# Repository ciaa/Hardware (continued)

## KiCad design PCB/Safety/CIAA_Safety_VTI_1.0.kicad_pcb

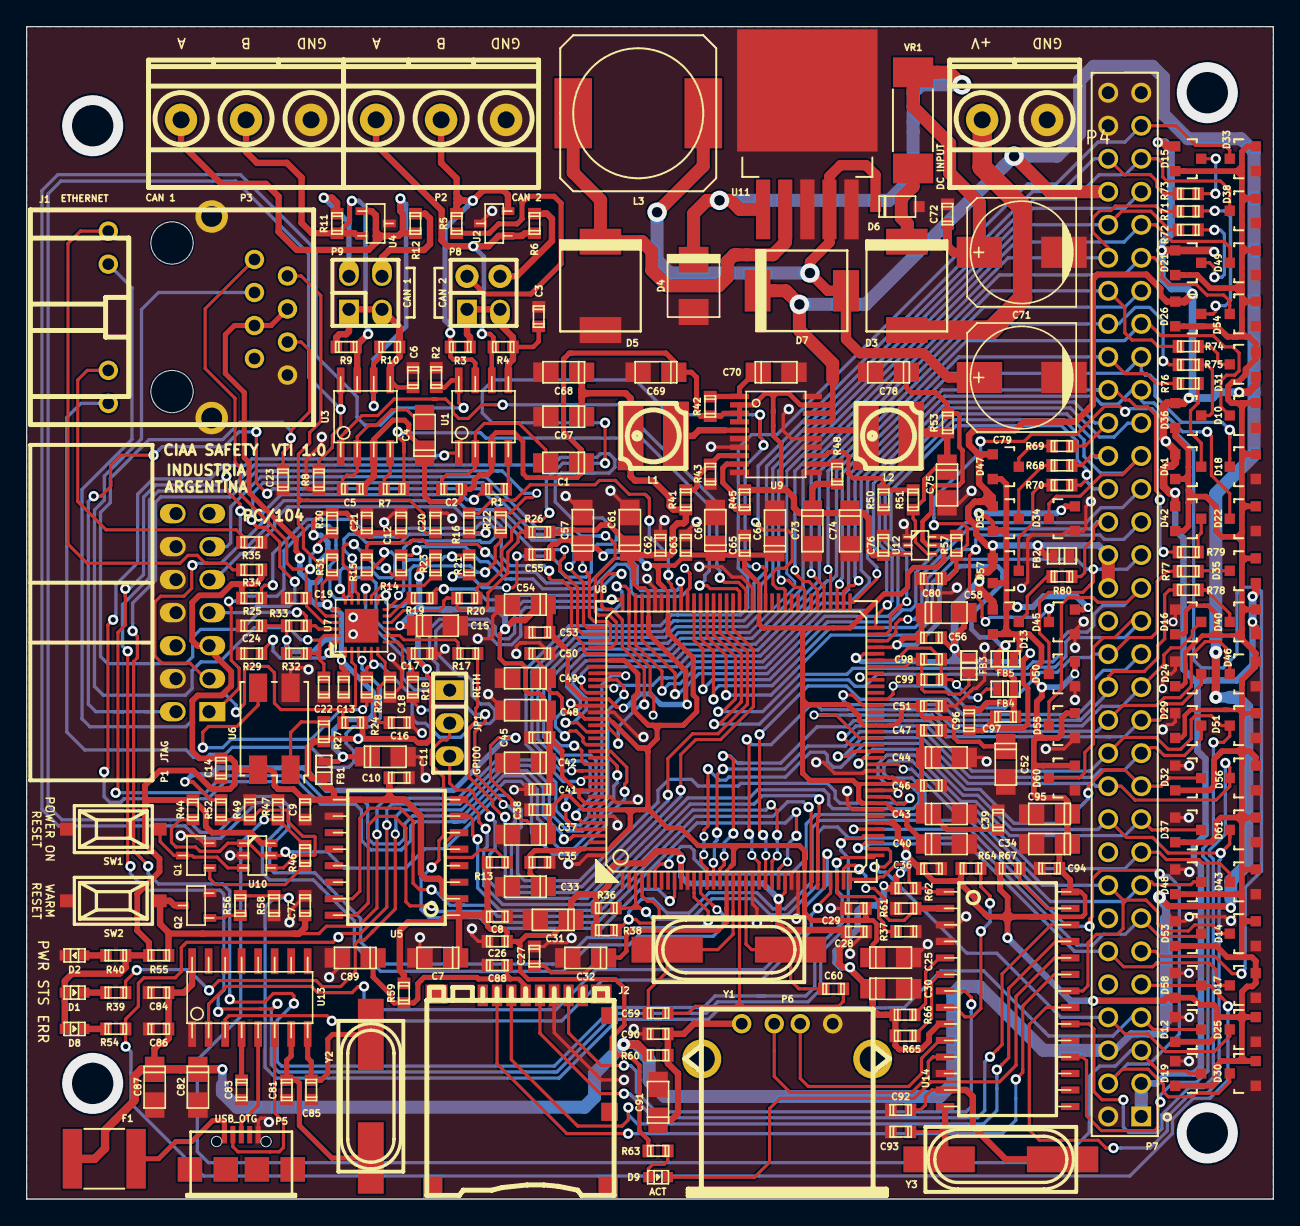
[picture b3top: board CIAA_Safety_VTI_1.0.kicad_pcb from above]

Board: 2 copper layers, 95.9 x 90.2 mm, 275 parts (0 on the bottom side), 191 nets.

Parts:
C1, C4, C7, C11, C15, C74, C82, C87, C89, C91, C95: 10uF-6.3V; c_tant_A
C2, C3, C5, C6, C8, C9, C10, C12, C13, C14, C17, C18, C21, C24, C26, C27, C28, C29, C35, C36, C38, C39, C41, C45, C46, C47, C50, C51, C53, C55, C56, C62, C63, C65, C72, C76, C83, C84, C86, C88, C90, C94, C98: 100nF; c_0603
C16: 470pF; c_0603
C19, C20, C22, C23: 18pF; c_0603
C25, C30, C31, C32, C33, C34, C37, C40, C42, C43, C44, C48, C49, C52, C54, C57, C58, C61, C64, C66: 10uF; c_tant_A
C59, C60: 33pF; c_0603
C67, C68, C69, C73, C75, C78: 22uF-6.3V; c_tant_A
C70: 1uF-6.3V; c_tant_A
C71: 470uF-50V; c_elec_8x10
C77: 1000pF; c_0603
C79: 330uF-16V; c_elec_8x10
C80: 4700pF; c_0603
C81, C85: 22pF; c_0603
C92, C93: 27pF; c_0603
C96, C97, C99: 10nF; c_0603
D1: STATUS; Led_0603
D2: PWR; Led_0603
D3, D7: MURS360; do214ab
D4: P6SMB33CA; do214aa
D5: MBRS540T3G; do214ab
D6: MMSZ5V6T1G; sod123
D8: ERR; Led_0603
D9: ACT; Led_0603
D10, D12, D13, D14, D15, D16, D17, D18, D19, D21, D22, D24, D25, D26, D29, D30, D31, D32, D33, D34, D35, D36, D37, D38, D40, D41, D42, D43, D45, D46, D47, D48, D49, D50, D51, D52, D53, D54, D55, D56, D57, D58, D60, D61: BAV199
F1: MF-SMDF050
FB1: BK1608HS220-T; inductor_smd_0603
FB2, FB5: MMZ1608B601C; inductor_smd_0603
FB3, FB4: ACML0603101; inductor_smd_0603
J1: HR911105A
J2: SD-CON; microsd_socket
JP1: JUMPER3; pin_strip_3
L1, L2: 1uH-3.1A; inductor_smd_4.8x2.8mm
L3: 47uH; SELF-WE-PD-XXL
P1: JTAG; vasch_strip_7x2_90
P2: CAN 2; mkds_1,5-3
P3: CAN 1; mkds_1,5-3
P4: DC INPUT; mkds_1,5-2
P5: USB_OTG; conn_usb_B_micro_smd-2
P6: USB_A; conn_usb_A
P7: CONN_02X32; bus_ISA_8bits
P8: CAN2; pin_socket_2x2
P9: CAN1; pin_socket_2x2
Q1, Q2: NDS7002A; sot23
R1, R7, R34, R35: 270; r_0603
R2, R8: 4K7; r_0603
R3, R4, R9, R10: 1.5K; r_0603
R5, R6, R11, R12: 60; r_0603
R13, R23, R24, R26, R36, R38, R43, R46, R50, R56, R68, R69, R70, R71, R72, R73, R74, R75, R76, R77, R78, R79, R80: 10K; r_0603
R14, R15, R16, R21, R22: 0; r_0603
R17, R18, R19, R20: 22; r_0603
R25: 1K5; r_0603
R27: 100K; r_0603
R28: 24.9; r_0603
R29: 12.1K; r_0603
R30, R31, R32, R33: 49,9; r_0603
R37, R39, R40, R44, R49, R52, R54, R55, R63: 2.2K; r_0603
R41, R57: 31.6K; r_0603
R42: 4.99; r_0603
R45, R48: 49.9K; r_0603
R47, R58: 330K; r_0603
R51: 5.76K; r_0603
R53: 0.010; r_0603
R59, R61, R62, R64, R65, R66, R67: 1K; r_0603
R60: 100; r_0603
SW1: POWER ON RESET; smd_push
SW2: WARM RESET; smd_push
U1, U3: SN65HVD1040; so-8
U2, U4: PESD1CAN; sot23
U5: S70FL01GS; soic-16
U6: Si502; Crystal_SMD_7050_4Pads
U7: LAN8720A-CP; qfn-24
U8: TMS570LS1227; TQFP-144
U9: LM26420; tssop-20
U10: TPS3106K33_DBV_6; sot23-6
U11: LM2596S-5.0; TO-263-5Lead
U12: INA210_DCK_6; sc70-6
U13: CH340G; so-16
U14: CH376S; soic-28
VR1: MF-SM300
Y1: 16MHz; hc-49_smd
Y2, Y3: 12MHz; hc-49_smd

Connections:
+1V2: C25.1, C27.1, C29.1, C32.1, C33.1, C35.2, C37.1, C38.2, C39.1, C40.1, C43.1, C44.1, C46.1, C47.1, C49.1, C50.2, C51.1, C52.1, C55.2, C57.1, C63.2, C64.1, C65.2, C66.1, C78.1, R52.1, R53.1, U8.17, U8.29, U8.45, U8.48, U8.49, U8.57, U8.87, U8.101, U8.114, U8.123, U8.137, U8.143, U12.5
+3.3VADC: C56.1, C58.1, C96.1, C97.1, FB4.1, FB5.2, U8.69
+3V3: C7.1, C8.1, C9.1, C10.1, C14.1, C15.1, C17.1, C26.1, C28.1, C30.1, C31.1, C34.1, C36.1, C41.2, C42.1, C45.2, C48.1, C53.2, C54.1, C61.1, C62.1, C67.1, C68.1, C94.1, C95.1, D1.2, D8.2, D10.1, D12.1, D13.1, D14.1, D15.1, D16.1, D17.1, D18.1, D19.1, D21.1, D22.1, D24.1, D25.1, D26.1, D29.1, D30.1, D31.1, D32.1, D33.1, D34.1, D35.1, D36.1, D37.1, D38.1, D40.1, D41.1, D42.1, D43.1, D45.1, D46.1, D47.1, D48.1, D49.1, D50.1, D51.1, D52.1, D53.1, D54.1, D55.1, D56.1, D57.1, D58.1, D60.1, D61.1, FB1.1, FB5.1, L1.1, P1.5, R13.2, R23.2, R24.2, R25.2, R26.2, R27.2, R34.2, R36.1, R38.1, R40.1, R41.2, R44.1, R55.1, R59.1, R62.1, R63.1, R64.1, R65.1, R66.1, R67.1, U5.1, U5.2, U5.9, U6.4, U7.9, U8.10, U8.26, U8.42, U8.104, U8.120, U8.134, U8.136, U10.6, U14.9, U14.28
+5V: C1.1, C2.1, C4.1, C5.1, C69.1, C73.1, C74.1, C76.1, C82.1, C84.1, C86.1, C87.1, D7.1, F1.2, P7.6, P7.58, R42.2, R45.2, R48.1, R60.1, U1.3, U3.3, U9.2, U9.3, U9.4, U9.17, U9.18, U9.19, U12.3, U13.16
/CAN 1/2/CAN1RX: R7.2, U8.90
/CAN 1/2/CAN1TX: U3.1, U8.89
/CAN 1/2/CAN1_H: P3.2, R9.1, R11.1, U3.7, U4.2
/CAN 1/2/CAN1_L: P3.3, R10.2, R12.1, U3.6, U4.1
/CAN 1/2/CAN1_STB: R8.1, U3.8, U8.12
/CAN 1/2/CAN2RX: R1.2, U8.129
/CAN 1/2/CAN2TX: U1.1, U8.128
/CAN 1/2/CAN2_H: P2.2, R3.1, R5.1, U1.7, U2.2
/CAN 1/2/CAN2_L: P2.3, R4.2, R6.1, U1.6, U2.1
/CAN 1/2/CAN2_STB: R2.1, U1.8, U8.13
/CPU/GPIO6: U8.32, U13.2
/CPU/GPIO7: U8.33, U13.3
/CPU/Kelvin_GND: C59.2, C60.1, U8.19
/CPU/MDCLK: R22.2, U8.37
/CPU/MDIO: R21.2, U8.40
/CPU/OSCIN: C59.1, U8.18, Y1.1
/CPU/OSCOUT: C60.2, U8.20, Y1.2
/CPU/RMII_CRS_DV: R19.2, U8.124
/CPU/RMII_REFCLK: R28.2, U7.5, U8.107
/CPU/RMII_RXD[0]: R17.2, U8.91
/CPU/RMII_RXD[1]: R18.2, U8.92
/CPU/RMII_RX_ER: R20.2, U8.86
/CPU/RMII_TXD[0]: R14.2, U8.98
/CPU/RMII_TXD[1]: R15.2, U8.99
/CPU/RMII_TXEN: R16.2, U8.100
/CPU/SPI4CLK: U5.16, U8.25
/CPU/SPI4NCS[0]: U5.7, U8.24
/CPU/SPI4SIMO[0]: U5.15, U8.30
/CPU/SPI4SOMI[0]: U5.8, U8.31
/CPU/STATUS: R39.2, U8.141
/CPU/nPORRST: R44.2, U8.46, U10.1, U10.5
/CPU/nRST: C77.1, Q2.D, R55.2, SW2.2, U8.116
/ETHERNET/LED_100M: J1.11, R24.1, U7.2
/ETHERNET/LED_LINK: J1.9, U7.3
/ETHERNET/RD+: C22.1, J1.3, R32.2, U7.23
/ETHERNET/RD-: C23.1, J1.6, R33.2, U7.22
/ETHERNET/TD+: C19.1, J1.1, R30.2, U7.21
/ETHERNET/TD-: C20.1, J1.2, R31.2, U7.20
/INT_A: R62.2, U8.36, U14.1
/ISA_AD1IN[0]: P7.28, R78.2, U8.60
/ISA_AD1IN[1]: P7.40, R70.2, U8.71
/ISA_AD1IN[2]: P7.44, R69.2, U8.73
/ISA_AD1IN[3]: P7.46, R79.2, U8.74
/ISA_AD1IN[4]: P7.50, R75.2, U8.76
/ISA_AD1IN[5]: P7.54, R71.2, U8.78
/ISA_AD1IN[6]: P7.56, R72.2, U8.80
/ISA_AD1IN[7]: P7.30, R77.2, U8.61
/ISA_AD1IN[8]: P7.60, R73.2, U8.83
/ISA_AD1IN[9]: P7.38, R80.2, U8.70
/ISA_AD1IN[10]: P7.42, R68.2, U8.72
/ISA_AD1IN[11]: P7.48, R76.2, U8.75
/ISA_AD1IN[12]: P7.52, R74.2, U8.77
/ISA_GPIO0: D37.2, JP1.3, P7.19
/ISA_GPIO0/RESET_ETH: JP1.2, U8.9
/ISA_GPIO1: D32.2, P7.21, U8.14
/ISA_GPIO2: D29.2, P7.23, U8.15
/ISA_GPIO3: D24.2, P7.25, U8.16
/ISA_GPIO4: D16.2, P7.27, U8.22
/ISA_GPIO5: P7.29, U8.23
/ISA_GPIO10: D30.2, P7.4, U8.41
/ISA_GPIO11: D60.2, P7.31, U8.93
/ISA_GPIO12: D55.2, P7.33, U8.94
/ISA_GPIO13: D50.2, P7.35, U8.95
/ISA_GPIO14: D45.2, P7.37, U8.96
/ISA_GPIO15: P7.39, U8.97
/ISA_GPIO16: D34.2, P7.41, U8.105
/ISA_GPIO17: P7.43, U8.106
/ISA_GPIO18: D22.2, P7.45, U8.118
/ISA_GPIO19: D18.2, P7.47, U8.119
/ISA_GPIO20: D10.2, P7.49, U8.125
/ISA_GPIO21: P7.51, U8.127
/ISA_GPIO22: D54.2, P7.53, U8.130
/ISA_GPIO23: D49.2, P7.55, U8.139
/ISA_GPIO24: P7.57, U8.140
/ISA_I2C_SCL: D53.2, P7.13, R36.2, U8.3
/ISA_I2C_SDA: D48.2, P7.15, R38.2, U8.4
/ISA_LINRX/GPIO35: D38.2, P7.59, U8.131
/ISA_LINTX/GPIO36: D33.2, P7.61, U8.132
/ISA_MIBSPI3CLK/GPIO32: D56.2, P7.22, U8.53, U14.20
/ISA_MIBSPI3NCS[0]/GPIO34: D46.2, P7.26, U8.55
/ISA_MIBSPI3NCS[4]/GPIO27: D43.2, P7.17, U8.6
/ISA_MIBSPI3NCS[5]/GPIO33: D51.2, P7.24, U8.54, U14.18
/ISA_MIBSPI3SIMO/GPIO31: D61.2, P7.20, U8.52, U14.21
/ISA_MIBSPI3SOMI/GPIO30: D14.2, P7.16, U8.51, U14.22
/ISA_MR: D19.2, P7.5, R46.1, R47.2
/ISA_SCIRX/GPIO28: D25.2, P7.8, U8.38
/ISA_SCITX/GPIO29: D17.2, P7.12, U8.39
/ISA_nERROR: D58.2, P7.9, R54.2, U8.117
/ISA_nRST: D12.2, P7.7, R56.1, R58.2
/RESET_ETH: JP1.1, U7.15
/RSTI_A: R61.1, U8.35, U14.2
/RTCK: P1.9, U8.113
/TCK: P1.11, U8.112
/TDI: P1.3, U8.110
/TDO: P1.7, U8.111
/TMS: P1.1, U8.108
/USB HOST - MEM SD/SD_CK: J2.5, U14.26
/USB HOST - MEM SD/SD_CS: J2.2, U14.23
/USB HOST - MEM SD/SD_DI: J2.3, U14.25
/USB HOST - MEM SD/SD_DO: J2.7, U14.7
/V_MONITOR: C80.1, P7.11, R57.1
/nTRST: P1.2, U8.109
GND: C3.2, C6.2, C7.2, C8.2, C9.2, C10.2, C11.2, C12.2, C13.2, C14.2, C15.2, C16.2, C17.2, C18.2, C19.2, C20.2, C21.2, C22.2, C23.2, C24.2, C25.2, C26.2, C27.2, C28.2, C29.2, C30.2, C31.2, C32.2, C33.2, C34.2, C35.1, C36.2, C37.2, C38.1, C39.2, C40.2, C41.1, C42.2, C43.2, C44.2, C45.1, C46.2, C47.2, C48.2, C49.2, C50.1, C51.2, C52.2, C53.1, C54.2, C55.1, C57.2, C61.2, C62.2, C63.1, C64.2, C65.1, C66.2, C67.2, C68.2, C69.2, C70.2, C71.2, C72.2, C73.2, C74.2, C75.2, C76.2, C77.2, C78.2, C79.2, C80.2, C81.1, C82.2, C83.1, C84.2, C85.1, C86.2, C87.2, C88.2, C89.2, C90.2, C91.2, C92.2, C93.2, C94.2, C95.2, D2.1, D4.1, D5.2, D6.2, D10.3, D12.3, D14.3, D16.3, D17.3, D18.3, D19.3, D22.3, D24.3, D25.3, D29.3, D30.3, D32.3, D33.3, D34.3, D37.3, D38.3, D43.3, D45.3, D46.3, D48.3, D49.3, D50.3, D51.3, D53.3, D54.3, D55.3, D56.3, D58.3, D60.3, D61.3, FB2.1, J1.8, J1.13, J2.6, P1.4, P1.8, P1.10, P1.12, P2.1, P3.1, P4.1, P5.5, P6.4, P7.2, P7.62, P7.63, P7.64, Q1.S, Q2.S, R2.2, R8.2, R29.1, R35.2, R37.2, R43.2, R47.1, R49.2, R50.2, R58.1, R61.2, SW1.1, SW2.1, U2.3, U4.3, U5.10, U6.2, U8.11, U8.21, U8.27, U8.28, U8.43, U8.44, U8.47, U8.50, U8.56, U8.88, U8.102, U8.103, U8.115, U8.121, U8.122, U8.135, U8.138, U8.144, U9.6, U9.7, U9.10, U9.11, U9.14, U9.15, U9.20, U10.2, U11.3, U11.5, U12.1, U12.2, U13.1, U14.3, U14.4, U14.12
GNDA: C56.2, C58.2, C96.2, C97.2, D13.3, D15.3, D21.3, D26.3, D31.3, D35.3, D36.3, D40.3, D41.3, D42.3, D47.3, D52.3, D57.3, FB2.2, FB3.1, P7.1, P7.3, P7.34, P7.36, U8.68
unnamed: C1.2, C2.2, U1.2
unnamed: C3.1, P8.1, P8.3, R3.2, R4.1, U1.5
unnamed: C4.2, C5.2, U3.2
unnamed: C6.1, P9.1, P9.3, R9.2, R10.1, U3.5
unnamed: C11.1, C12.1, C13.1, C21.1, C24.1, FB1.2, J1.4, J1.5, R30.1, R31.1, R32.1, R33.1, U7.1, U7.19
unnamed: C16.1, C18.1, U7.6
unnamed: C70.1, R42.1, U9.1
unnamed: C71.1, C72.1, D4.2, U11.1, VR1.1
unnamed: C75.1, L2.2, R51.1, R53.2, U12.4
unnamed: C79.1, D6.1, D7.2, L3.2, U11.4
unnamed: C81.2, U13.7, Y2.1
unnamed: C83.2, U13.4
unnamed: C85.2, U13.8, Y2.2
unnamed: C88.1, C89.1, J2.4, R59.2
unnamed: C90.1, C91.1, P6.1, R60.2
unnamed: C92.1, U14.13, Y3.1
unnamed: C93.1, U14.14, Y3.2
unnamed: C98.1, C99.1, FB4.2, U8.67
unnamed: C98.2, C99.2, FB3.2, U8.66
unnamed: D1.1, R39.1
unnamed: D2.2, R40.2
unnamed: D3.1, VR1.2
unnamed: D3.2, P4.2
unnamed: D5.1, L3.1, U11.2
unnamed: D8.1, R54.1
unnamed: D9.1, U14.24
unnamed: D9.2, R63.2
unnamed: D13.2, R80.1
unnamed: D15.2, R73.1
unnamed: D21.2, R72.1
unnamed: D26.2, R71.1
unnamed: D31.2, R74.1
unnamed: D35.2, R77.1
unnamed: D36.2, R75.1
unnamed: D40.2, R78.1
unnamed: D41.2, R76.1
unnamed: D42.2, R79.1
unnamed: D47.2, R69.1
unnamed: D52.2, R68.1
unnamed: D57.2, R70.1
unnamed: F1.1, P5.1
unnamed: J1.10, R35.1
unnamed: J1.12, R34.1
unnamed: L1.2, U9.5
unnamed: L2.1, U9.16
unnamed: P5.2, U13.6
unnamed: P5.3, U13.5
unnamed: P6.2, U14.11
unnamed: P6.3, U14.10
unnamed: P8.2, R5.2
unnamed: P8.4, R6.2
unnamed: P9.2, R11.2
unnamed: P9.4, R12.2
unnamed: Q1.D, SW1.2, U10.3
unnamed: Q1.G, R46.2
unnamed: Q2.G, R56.2
unnamed: R1.1, U1.4
unnamed: R7.1, U3.4
unnamed: R13.1, U5.6
unnamed: R14.1, U7.17
unnamed: R15.1, U7.18
unnamed: R16.1, U7.16
unnamed: R17.1, U7.8
unnamed: R18.1, U7.7
unnamed: R19.1, U7.11
unnamed: R20.1, R26.1, U7.10
unnamed: R21.1, R25.1, U7.12
unnamed: R22.1, U7.13
unnamed: R23.1, U7.14
unnamed: R27.1, U6.1
unnamed: R28.1, U6.3
unnamed: R29.2, U7.24
unnamed: R37.1, U8.34
unnamed: R41.1, R43.1, U9.8
unnamed: R45.1, U9.9
unnamed: R48.2, U9.12
unnamed: R49.1, R52.2, U10.4
unnamed: R50.1, R51.2, U9.13
unnamed: R57.2, U12.6
unnamed: R64.2, U14.8
unnamed: R65.2, U14.6
unnamed: R66.2, U14.5
unnamed: R67.2, U14.27

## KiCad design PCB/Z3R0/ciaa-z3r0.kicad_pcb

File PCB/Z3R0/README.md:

# CIAA-Z3R0

Here you will find KiCad design files, [gerber files](gerbers) and [documentation](docs) for this board developed by Eric Pernia.

Also you can visit [CIAA-Z3R0 Wiki Page](http://www.proyecto-ciaa.com.ar/devwiki/doku.php?id=desarrollo:ciaa-z3r0).

 - [Authors](AUTHORS.md).
 - License: [CIAA Hardware license](LICENSE).

## Board description

This board is designed for low cost, low power consumption and robotics applications.

### Schematic

[Schematic in pdf](ciaa-z3r0.pdf)

### 3D view

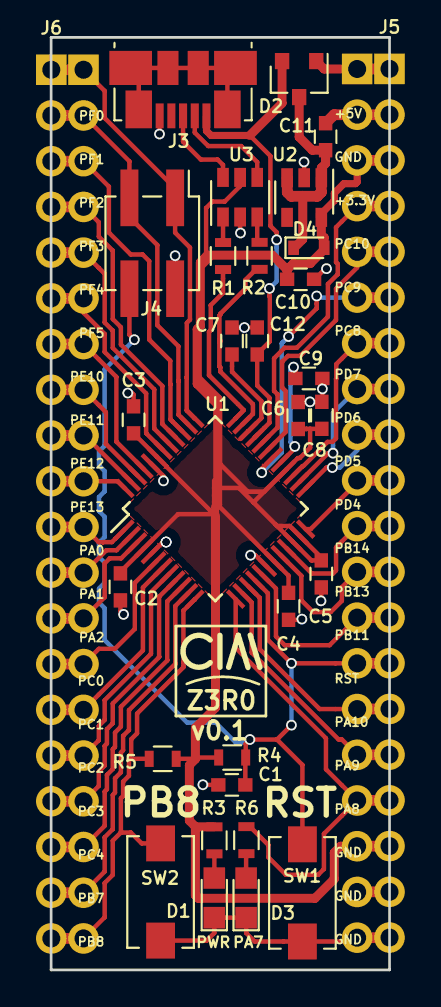
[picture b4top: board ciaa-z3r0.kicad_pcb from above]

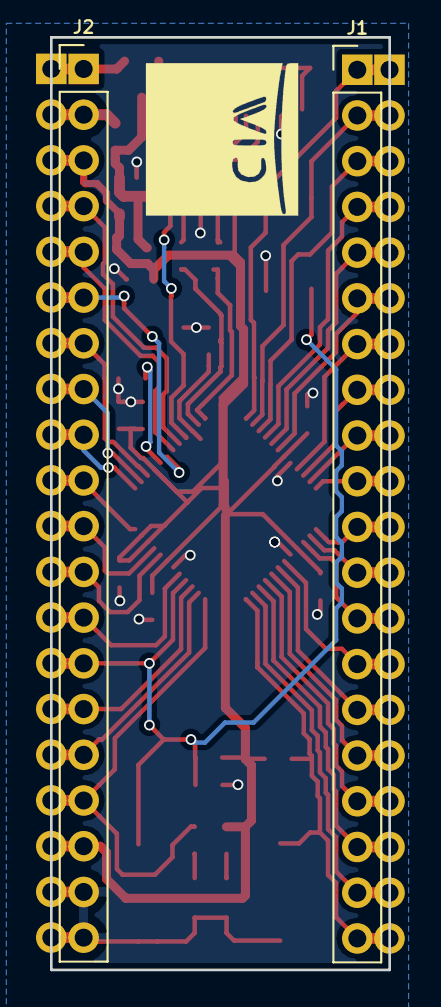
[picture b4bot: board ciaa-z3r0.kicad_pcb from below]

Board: 2 copper layers, 18.8 x 51.8 mm, 34 parts (3 on the bottom side), 49 nets.

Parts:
C1, C7, C9, C10, C11: 1u; C_0603
C2, C3, C4, C5, C6: 100n; C_0603
C8: 10u; C_0603
C12: 4.7u; C_0603
D1: PWR; LED_0805
D2: PMEG2005CT; SOT-23
D3: PA8; LED_0805
D4: SD0603S040S0R2; D_0603
G102: LOGO_CIAA; LOGO-CIAA
J1, J2: Conn_01x20; Pin_Header_Straight_1x20_Pitch2.54mm
J3: USB_OTG; USB_Micro-B_Molex_47346-0001
J4: SWD; Pin_Header_Straight_2x02_Pitch2.54mm_SMD
J5, J6: Conn_01x20; Pin_Header_Straight_1x20_Pitch2.54mm_nosilkscreen
R1, R2: 15R; R_0603
R3, R4, R5, R6: 1K; R_0603
SW1, SW2: reset; SW_SPST_EVQPE1
U1: EFM32HG-48LQFP; LQFP-48_7x7mm_Pitch0.5mm
U2: SPX3819M5-L-3-3; SOT-23-5
U3: USBLC6-2; SOT-23-6

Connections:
+3V3: C2.1, C3.1, C4.2, C5.2, C6.1, C8.1, C10.1, D4.2, J2.3, J2.18, J5.3, J5.18, R3.2, R4.1, R5.1, U1.4, U1.19, U1.22, U1.23, U1.28, U1.43, U2.5, U3.5
+5V: C11.1, D2.3, D4.1, U2.1, U2.3
/B_USB+: J3.3, U3.6
/B_USB-: J3.2, U3.4
/PA0: J1.11, J6.11, U1.1
/PA1: J1.12, J6.12, U1.2
/PA2: J1.13, J6.13, U1.3
/PA8: J2.17, J5.17, R6.2, U1.13
/PA9: J2.16, J5.16, U1.14
/PA10: J2.15, J5.15, U1.15
/PB7: J1.19, J6.19, U1.11
/PB8: J1.20, J6.20, R5.2, SW2.2, U1.12
/PB11: J2.13, J5.13, U1.17
/PB13: J2.12, J5.12, U1.20
/PB14: J2.11, J5.11, U1.21
/PC0: J1.14, J6.14, U1.6
/PC1: J1.15, J6.15, U1.7
/PC2: J1.16, J6.16, U1.8
/PC3: J1.17, J6.17, U1.9
/PC4: J1.18, J6.18, U1.10
/PC8: J2.6, J5.6, U1.30
/PC9: J2.5, J5.5, U1.31
/PC10: J2.4, J5.4, U1.32
/PD4: J2.10, J5.10, U1.24
/PD5: J2.9, J5.9, U1.25
/PD6: J2.8, J5.8, U1.26
/PD7: J2.7, J5.7, U1.27
/PE10: J1.7, J6.7, U1.45
/PE11: J1.8, J6.8, U1.46
/PE12: J1.9, J6.9, U1.47
/PE13: J1.10, J6.10, U1.48
/PF0/SWCLK: J1.1, J4.1, J6.1, U1.37
/PF1/SWDIO: J1.2, J4.3, J6.2, U1.38
/PF2: J1.3, J6.3, U1.39
/PF3: J1.4, J6.4, U1.40
/PF4: J1.5, J6.5, U1.41
/PF5: J1.6, J6.6, U1.42
/USB+: R1.2, U1.36
/USB-: R2.2, U1.35
/nRESET: C1.2, J2.14, J4.4, J5.14, R4.2, SW1.2, U1.16
/vin: D2.1, J2.1, J5.1
/vusb: C12.1, D2.2, J3.1, U1.33
GND: C1.1, C2.2, C3.2, C4.1, C5.1, C6.2, C7.2, C8.2, C9.2, C10.2, C11.2, C12.2, D1.1, D3.1, J2.2, J2.19, J2.20, J3.5, J4.2, J5.2, J5.19, J5.20, SW1.1, SW2.1, U1.5, U1.18, U1.44, U2.2, U3.2
unnamed: C7.1, U1.34
unnamed: C9.1, U1.29
unnamed: D1.2, R3.1
unnamed: D3.2, R6.1
unnamed: R1.1, U3.1
unnamed: R2.1, U3.3

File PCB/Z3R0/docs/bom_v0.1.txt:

Reference       Quantity    Value               Footprint                        Part number              digikey part number
C12                 1       4.7u                Capacitor 0603                   CC0603KRX5R7BB475        311-1785-1-ND
C2 C3 C4 C5 C6      5       100n                Capacitor 0603                   CC0603KRX7R7BB104        311-1088-1-ND
C8                  1       10u                 Capacitor 0603                   GRM188R61C106KAALD       490-10728-1-ND
C1 C10 C11 C7 C9    5       1u                  Capacitor 0603                   CC0603KRX7R7BB105        311-1446-1-ND
D1 D3               2       LED GREEN           LED 0805                         LTST-C170GKT             160-1179-1-ND
D2                  1       PMEG2005CT          SOT-23-3                         PMEG2005CT,215           1727-5188-1-ND
D4                  1       SD0603S040S0R2      Diode 0603                       SD0603S040S0R2           478-7798-1-ND
U1                  1       EFM32HG-48LQFP      LQFP-48 7x7mm                    EFM32HG222F64G-B-QFP48   336-3894-ND
U2                  1       SPX3819M5-L-3-3     SOT-23-5                         SPX3819M5-L-3-3/TR       1016-1873-1-ND
U3                  1       USBLC6-2            SOT-23-6                         USBLC6-2SC6              497-5235-1-ND
SW1 SW2             2       Switch EVQ-PE105K   Switch SPST-NO 6mm x 3.5mm       EVQ-PE105K               P13594SCT-ND
J3                  1       USB Micro-B         USB_Micro-B_Molex_47346-0001     Molex 473460001          WM17141CT-ND
J4                  1       Header SMD 2x2      Pin Header 2x2 Pitch 2.54mm SMD  M20-8760242              952-3254-ND
R1 R2               2       15R                 Resistor 0603                    RC0603JR-0715RL          311-15GRCT-ND
R3 R4 R5 R6         4       1K                  Resistor 0603                    RC0603JR-0710KL          311-10KGRCT-ND

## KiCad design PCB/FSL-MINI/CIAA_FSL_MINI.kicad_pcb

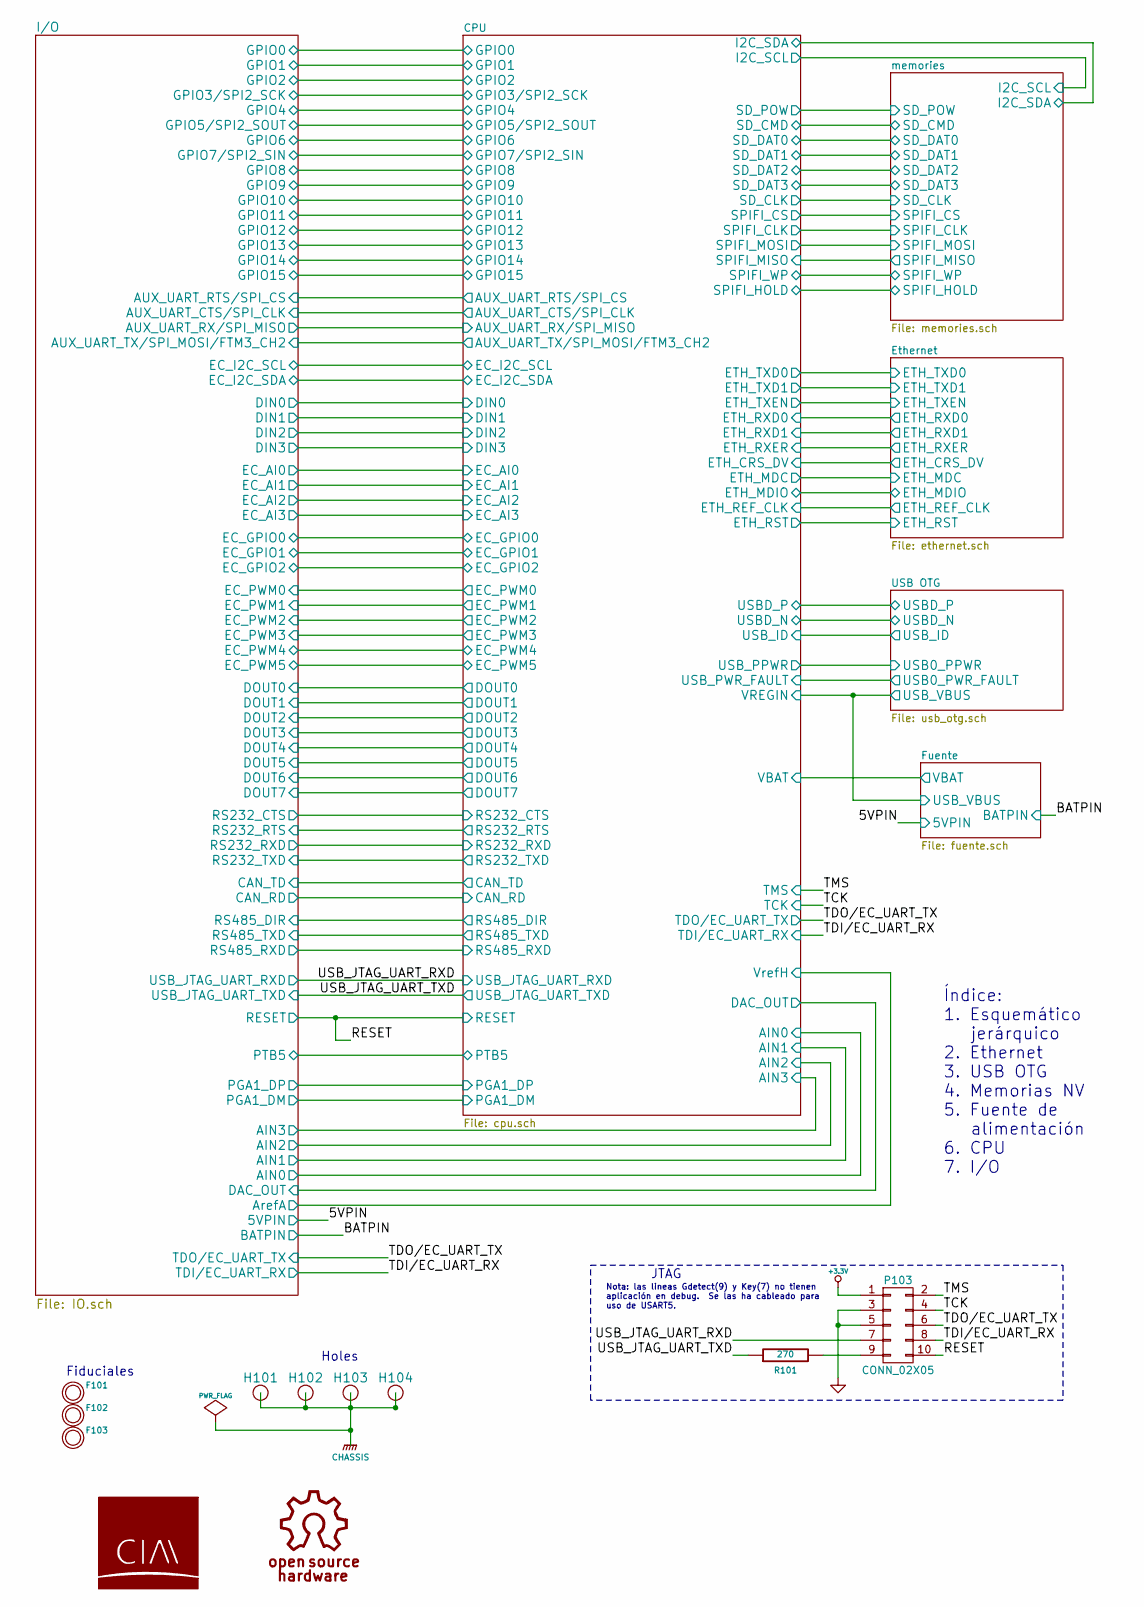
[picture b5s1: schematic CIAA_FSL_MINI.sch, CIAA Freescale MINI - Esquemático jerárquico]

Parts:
F101, F102, F103: FIDUCIAL; Fiducial_1mm
G101: LOGO_CIAA; LOGO-CIAA
G102: OSHWA
H101, H102, H103, H104: PCB_HOLE
P103: CONN_02X05; Pin_Header_Straight_2x05_Pitch1.27mm
R101: 270; r_0603

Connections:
/RESET: P103.10; also elsewhere on the board
/TCK: P103.4; also elsewhere on the board
/TDI/EC_UART_RX: P103.8; also elsewhere on the board
/TDO/EC_UART_TX: P103.6; also elsewhere on the board
/TMS: P103.2; also elsewhere on the board
/USB_JTAG_UART_RXD: P103.7; also elsewhere on the board
/USB_JTAG_UART_TXD: R101.1; also elsewhere on the board
GND: P103.3, P103.5; also elsewhere on the board
GNDPWR: H101.1, H102.1, H103.1, H104.1; also elsewhere on the board
unnamed: P103.9, R101.2

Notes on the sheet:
Índice: 1. Esquemático jerárquico 2. Ethernet 3. USB OTG 4. Memorias NV 5. Fuente de alimentación 6. CPU 7. I/O
Fiduciales
Holes
Nota: las lineas Gdetect(9) y Key(7) no tienen aplicación en debug. Se las ha cableado para uso de USART5.
JTAG

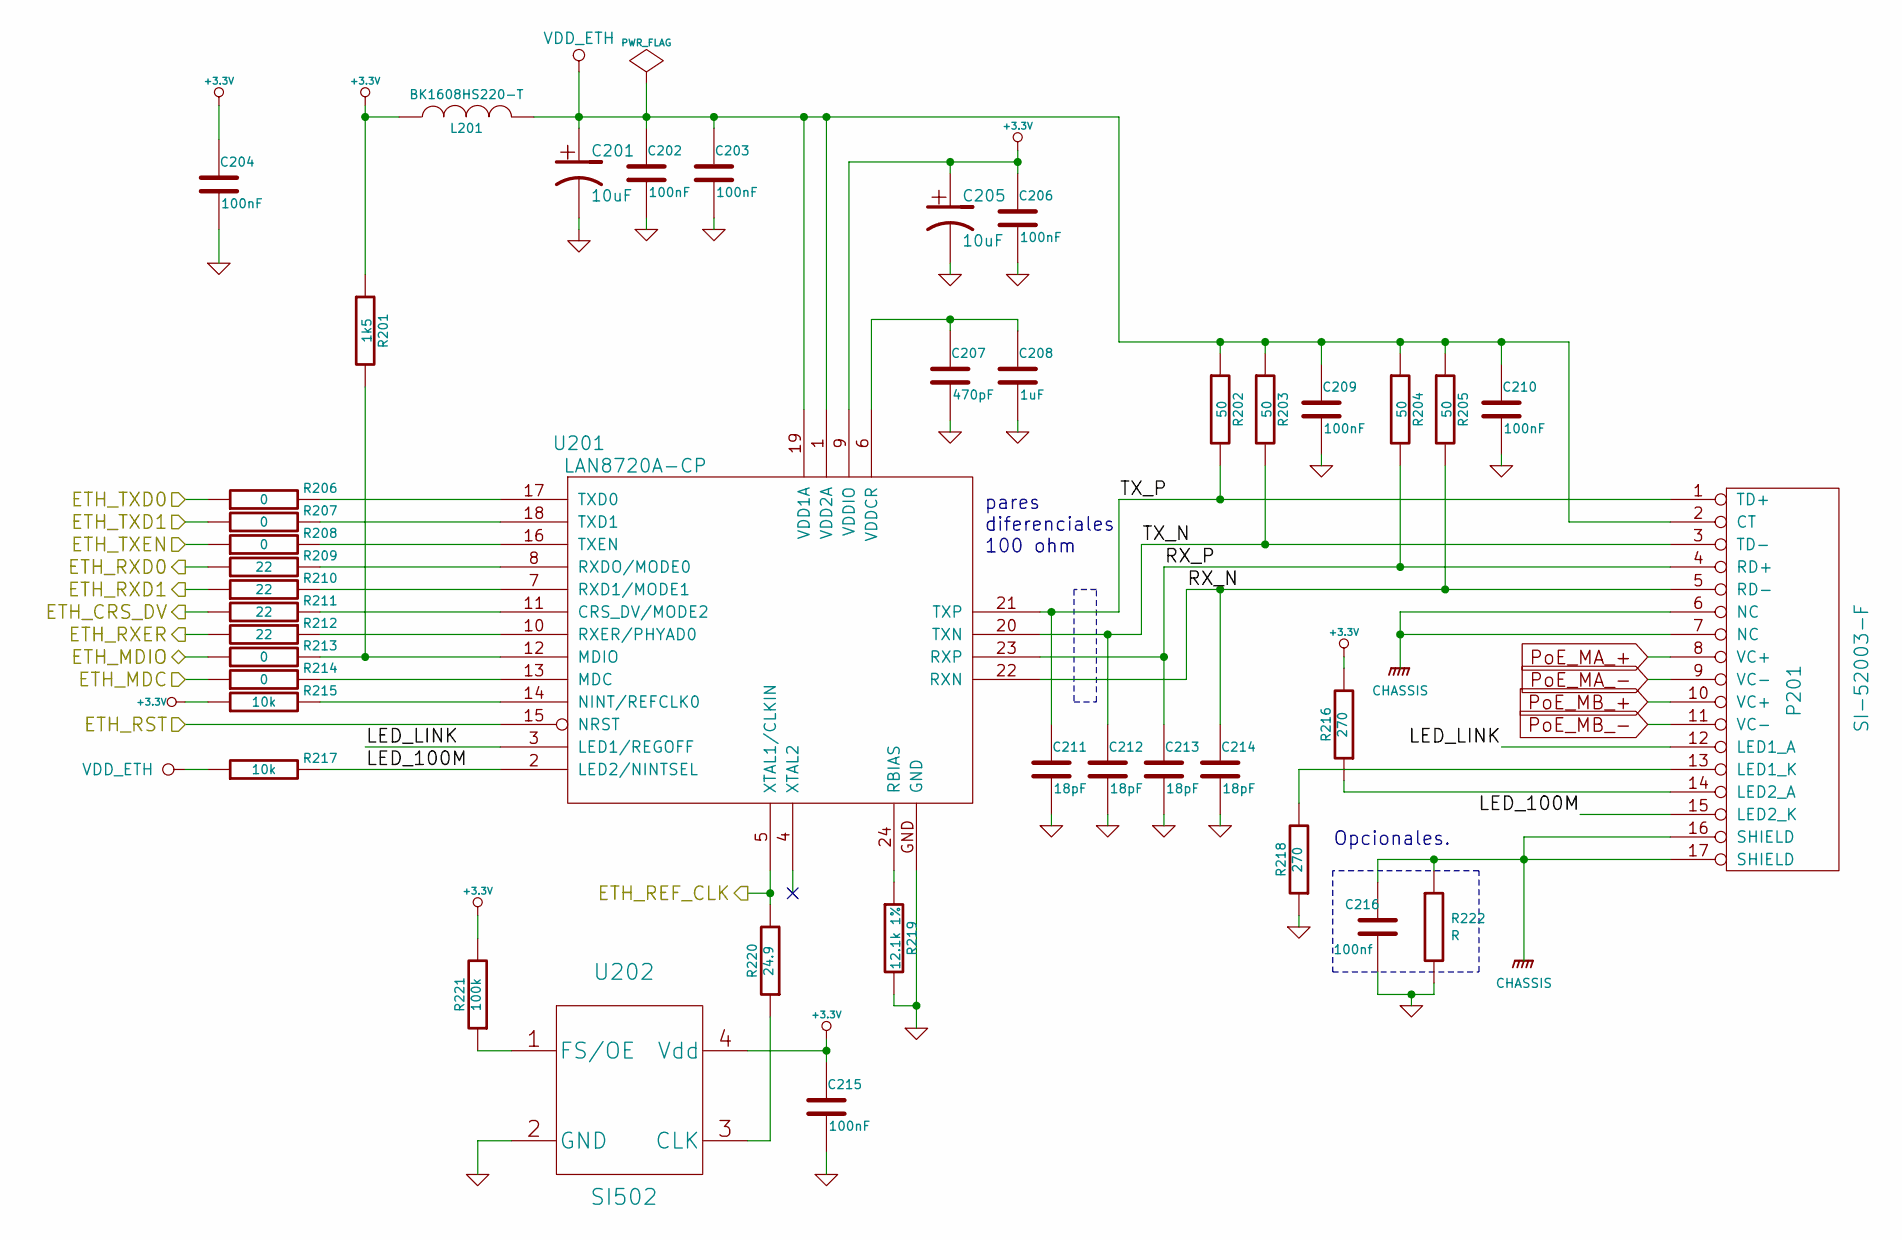
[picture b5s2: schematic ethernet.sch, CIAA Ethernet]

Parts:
C201, C205: 10uF; c_1206POL
C202, C203, C204, C206, C209, C210, C215: 100nF; c_0603
C207: 470pF; c_0603
C208: 1uF; c_0603
C211, C212, C213, C214: 18pF; c_0603
C216: 100nf; c_0603
L201: BK1608HS220-T; fb_0603
P201: SI-52003-F; RJ45_SI-52003-F_PoE_ETH
R201: 1k5; r_0603
R202, R203, R204, R205: 50; r_0603
R206, R207, R208, R213, R214: 0; r_0603
R209, R210, R211, R212: 22; r_0603
R215, R217: 10k; r_0603
R216, R218: 270; r_0603
R219: 12.1k 1%; r_0603
R220: 24.9; r_0603
R221: 100k; r_0603
R222: R; r_0603
U201: LAN8720A-CP; QFN-24-1EP_4x4mm_Pitch0.5mm
U202: SI502; Oscillator_7.0x5.0mm

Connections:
/CPU/ETH_CRS_DV: R211.1; also elsewhere on the board
/CPU/ETH_MDC: R214.1; also elsewhere on the board
/CPU/ETH_MDIO: R213.1; also elsewhere on the board
/CPU/ETH_REF_CLK: R220.2, U201.5 (XTAL1/CLKIN); also elsewhere on the board
/CPU/ETH_RST: U201.15 (NRST); also elsewhere on the board
/CPU/ETH_RXD0: R209.1; also elsewhere on the board
/CPU/ETH_RXD1: R210.1; also elsewhere on the board
/CPU/ETH_RXER: R212.2; also elsewhere on the board
/CPU/ETH_TXD0: R206.1; also elsewhere on the board
/CPU/ETH_TXD1: R207.1; also elsewhere on the board
/CPU/ETH_TXEN: R208.1; also elsewhere on the board
/Ethernet/LED_100M: P201.15 (LED2_K), R217.2, U201.2 (LED2/NINTSEL)
/Ethernet/LED_LINK: P201.12 (LED1_A), U201.3 (LED1/REGOFF)
/Ethernet/RX_N: C214.1, P201.5 (RD-), R205.2, U201.22 (RXN)
/Ethernet/RX_P: C213.1, P201.4 (RD+), R204.2, U201.23 (RXP)
/Ethernet/TX_N: C212.1, P201.3 (TD-), R203.2, U201.20 (TXN)
/Ethernet/TX_P: C211.1, P201.1 (TD+), R202.2, U201.21 (TXP)
GND: C201.2, C202.2, C203.2, C204.2, C205.2, C206.2, C207.2, C208.2, C209.2, C210.2, C211.2, C212.2, C213.2, C214.2, C215.2, C216.2, R218.1, R219.2, R222.2, U201.GND, U202.2 (GND); also elsewhere on the board
GNDPWR: C216.1, P201.6 (NC), P201.7 (NC), P201.16 (SHIELD), P201.17 (SHIELD), R222.1; also elsewhere on the board
unnamed: C207.1, C208.1, U201.6 (VDDCR)
unnamed: P201.13 (LED1_K), R218.2
unnamed: P201.14 (LED2_A), R216.1
unnamed: R201.2, R213.2, U201.12 (MDIO)
unnamed: R206.2, U201.17 (TXD0)
unnamed: R207.2, U201.18 (TXD1)
unnamed: R208.2, U201.16 (TXEN)
unnamed: R209.2, U201.8 (RXDO/MODE0)
unnamed: R210.2, U201.7 (RXD1/MODE1)
unnamed: R211.2, U201.11 (CRS_DV/MODE2)
unnamed: R212.1, U201.10 (RXER/PHYAD0)
unnamed: R214.2, U201.13 (MDC)
unnamed: R215.2, U201.14 (NINT/REFCLK0)
unnamed: R219.1, U201.24 (RBIAS)
unnamed: R220.1, U202.3 (CLK)
unnamed: R221.1, U202.1 (FS/OE)
PoE_MA_+: P201.8 (VC+); also elsewhere on the board
PoE_MA_-: P201.9 (VC-); also elsewhere on the board
PoE_MB_+: P201.10 (VC+); also elsewhere on the board
PoE_MB_-: P201.11 (VC-); also elsewhere on the board
VDD_ETH: C201.1, C202.1, C203.1, C209.1, C210.1, L201.2, P201.2 (CT), R202.1, R203.1, R204.1, R205.1, R217.1, U201.1 (VDD2A), U201.19 (VDD1A)

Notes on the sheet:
Opcionales.
pares diferenciales 100 ohm

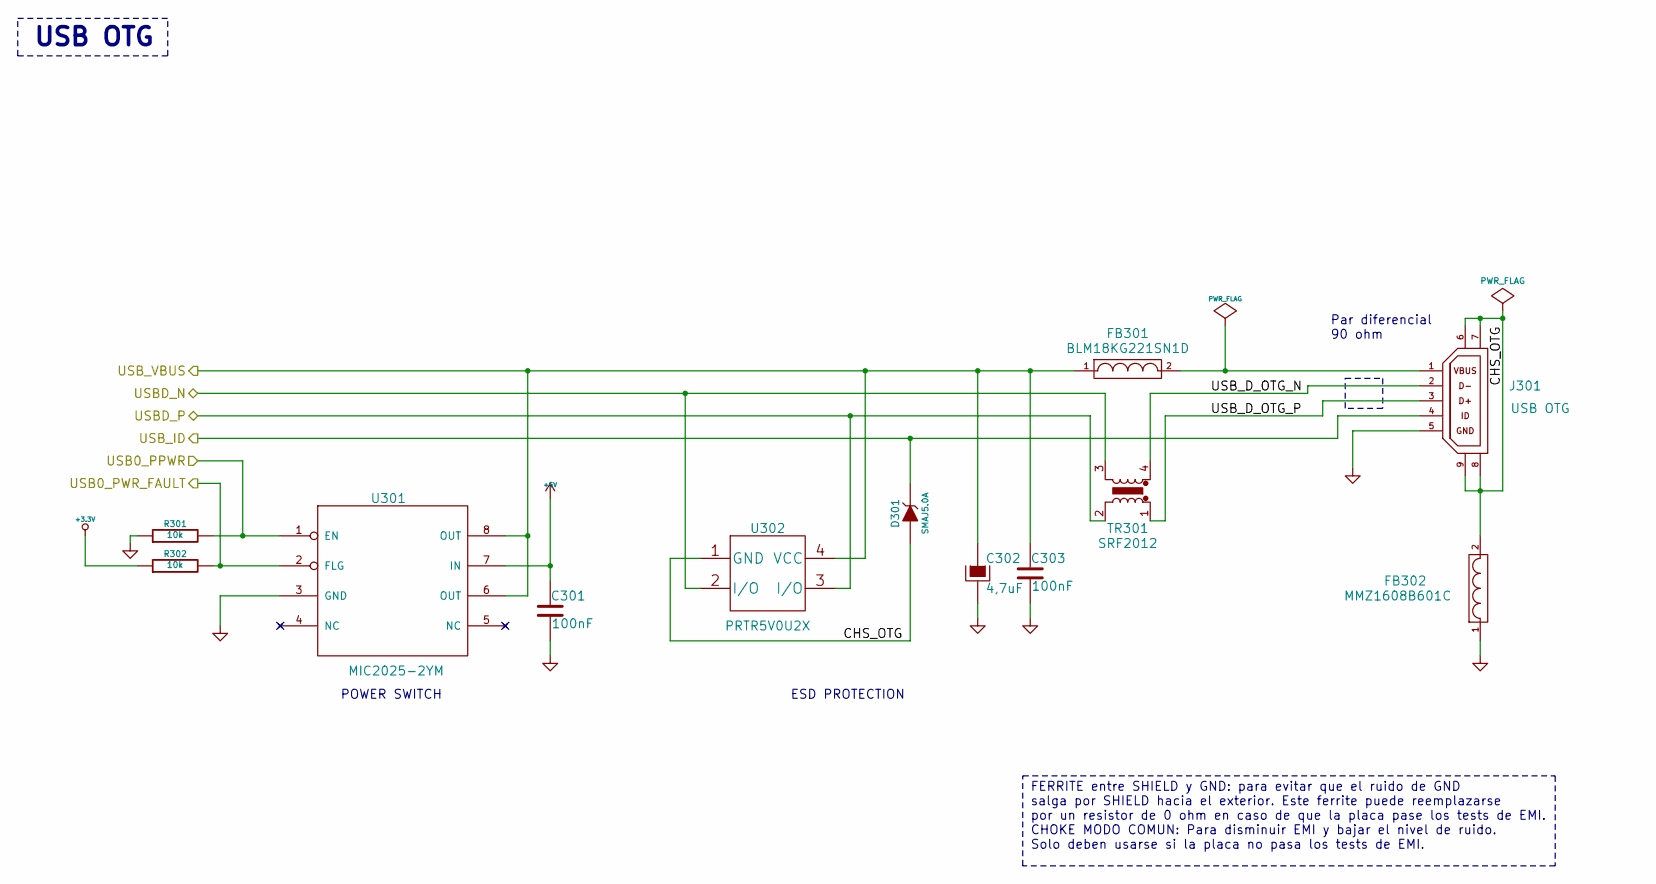
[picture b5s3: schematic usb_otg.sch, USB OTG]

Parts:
C301, C303: 100nF; c_0603; Digikey/Mouser 399-1096-1-ND
C302: 4,7uF; c_1206POL; Digikey/Mouser 399-9717-1-ND
D301: SMAJ5.0A; DO-214AC_SMA; Digikey/Mouser SMAJ5.0ABCT-ND
FB301: BLM18KG221SN1D; fb_0603; Digikey/Mouser 490-5255-1-ND
FB302: MMZ1608B601C; fb_0603; Digikey/Mouser 445-2166-1-ND
J301: USB OTG; USB_MicroAB; Digikey/Mouser H11635TR-ND
R301, R302: 10k; r_0603; Digikey/Mouser 311-10KGRCT-ND
TR301: SRF2012; Digikey/Mouser SRF2012-900YCT-ND
U301: MIC2025-2YM; SOIC-8; Digikey/Mouser 576-1058-ND
U302: PRTR5V0U2X; SOT-143-4; Digikey/Mouser CM1213A-02SROSCT-ND

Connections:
+5V: C301.1, U301.7 (IN); also elsewhere on the board
/CPU/USBD_N: TR301.3, U302.2 (I/O); also elsewhere on the board
/CPU/USBD_P: TR301.2, U302.3 (I/O); also elsewhere on the board
/CPU/USB_ID: D301.2 (K), J301.4 (USB_ID); also elsewhere on the board
/USB OTG/CHS_OTG: D301.1 (A), FB302.2, J301.6 (S2), J301.7 (S1), J301.8 (S3), J301.9 (S4), U302.1 (GND)
/USB OTG/USB0_PPWR: R301.2, U301.1 (EN); also elsewhere on the board
/USB OTG/USB0_PWR_FAULT: R302.2, U301.2 (FLG); also elsewhere on the board
/USB OTG/USB_D_OTG_N: J301.2 (USB_DN), TR301.4
/USB OTG/USB_D_OTG_P: J301.3 (USB_DP), TR301.1
/USB_VBUS: C302.1, C303.1, FB301.1, U301.6 (OUT), U301.8 (OUT), U302.4 (VCC); also elsewhere on the board
GND: C301.2, C302.2, C303.2, FB302.1, J301.5 (GND), R301.1, U301.3 (GND); also elsewhere on the board
unnamed: FB301.2, J301.1 (VBUS)

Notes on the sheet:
USB OTG
Par diferencial 90 ohm
FERRITE entre SHIELD y GND: para evitar que el ruido de GND salga por SHIELD hacia el exterior. Este ferrite puede reemplazarse por un resistor de 0 ohm en caso de que la placa pase los tests de EMI. CHOKE MODO COMUN: Para disminuir EMI y bajar el nivel de ruido. Solo deben usarse si la placa no pa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
POWER SWITCH
ESD PROTECTION
